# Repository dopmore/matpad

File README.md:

# matpad
a macropad for hackclub and CAD with EC11 rotary Encoder

Heres the final Version!

https://github.com/user-attachments/assets/6c2f23e0-6682-42b4-9371-2d59c67244ef

# BOM:

    - 16x Cherry MX Switches (+1 Just in Case?)
    - 15x DSA Keycaps
    - 16x Diodes (1N4148)
    - 4x M3x5x4 Heatset inserts (After I build the PCB i might remake the case to use screws)
    - 4x M3x16mm SHCS Bolts
    - 1x EC11 Rotary Encoder
    - 1x XIAO RP2040
    - 1x custom PCB

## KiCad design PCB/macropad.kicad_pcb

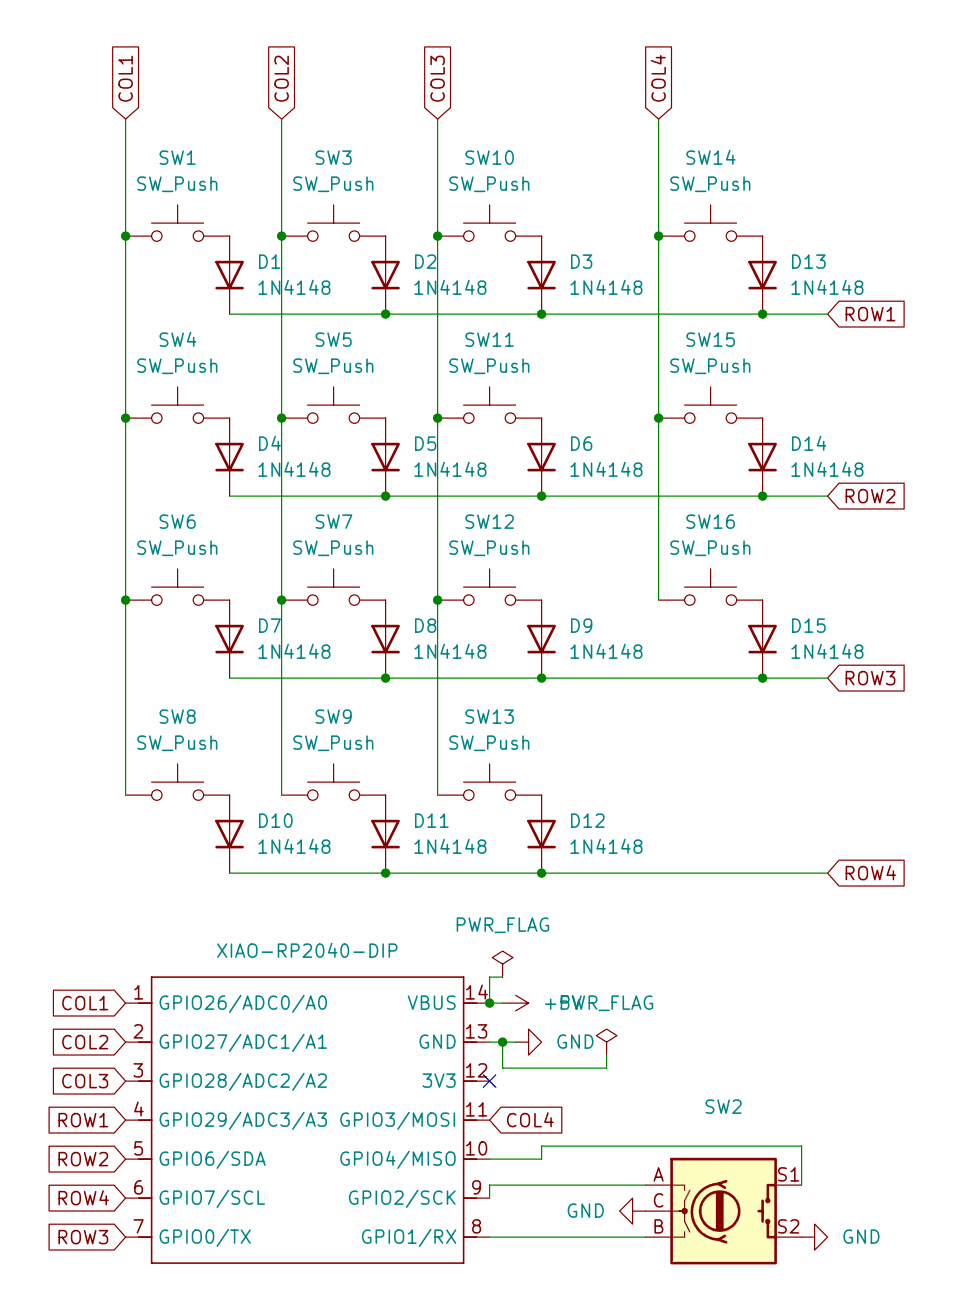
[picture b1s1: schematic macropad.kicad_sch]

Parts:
D1, D2, D3, D4, D5, D6, D7, D8, D9, D10, D11, D12, D13, D14, D15: 1N4148; D_DO-35_SOD27_P7.62mm_Horizontal
SW1, SW3, SW4, SW5, SW6, SW7, SW8, SW9, SW10, SW11, SW12, SW13, SW14, SW15, SW16: SW_Push; SW_Cherry_MX_1.00u_PCB
SW2: RotaryEncoder_Switch; RotaryEncoder_Alps_EC11E-Switch_Vertical_H20mm
U1: XIAO-RP2040-DIP

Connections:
+5V: U1.14 (VBUS)
COL1: SW1.1, SW4.1, SW6.1, SW8.1, U1.1 (GPIO26/ADC0/A0)
COL2: SW3.1, SW5.1, SW7.1, SW9.1, U1.2 (GPIO27/ADC1/A1)
COL3: SW10.1, SW11.1, SW12.1, SW13.1, U1.3 (GPIO28/ADC2/A2)
COL4: SW14.1, SW15.1, SW16.1, U1.11 (GPIO3/MOSI)
GND: SW2.C, SW2.S2, U1.13 (GND)
unnamed: D1.2 (A), SW1.2
unnamed: D2.2 (A), SW3.2
unnamed: D3.2 (A), SW10.2
unnamed: D4.2 (A), SW4.2
unnamed: D5.2 (A), SW5.2
unnamed: D6.2 (A), SW11.2
unnamed: D7.2 (A), SW6.2
unnamed: D8.2 (A), SW7.2
unnamed: D9.2 (A), SW12.2
unnamed: D10.2 (A), SW8.2
unnamed: D11.2 (A), SW9.2
unnamed: D12.2 (A), SW13.2
unnamed: D13.2 (A), SW14.2
unnamed: D14.2 (A), SW15.2
unnamed: D15.2 (A), SW16.2
unnamed: SW2.B, U1.8 (GPIO1/RX)
unnamed: SW2.A, U1.9 (GPIO2/SCK)
unnamed: SW2.S1, U1.10 (GPIO4/MISO)
ROW1: D1.1 (K), D2.1 (K), D3.1 (K), D13.1 (K), U1.4 (GPIO29/ADC3/A3)
ROW2: D4.1 (K), D5.1 (K), D6.1 (K), D14.1 (K), U1.5 (GPIO6/SDA)
ROW3: D7.1 (K), D8.1 (K), D9.1 (K), D15.1 (K), U1.7 (GPIO0/TX)
ROW4: D10.1 (K), D11.1 (K), D12.1 (K), U1.6 (GPIO7/SCL)

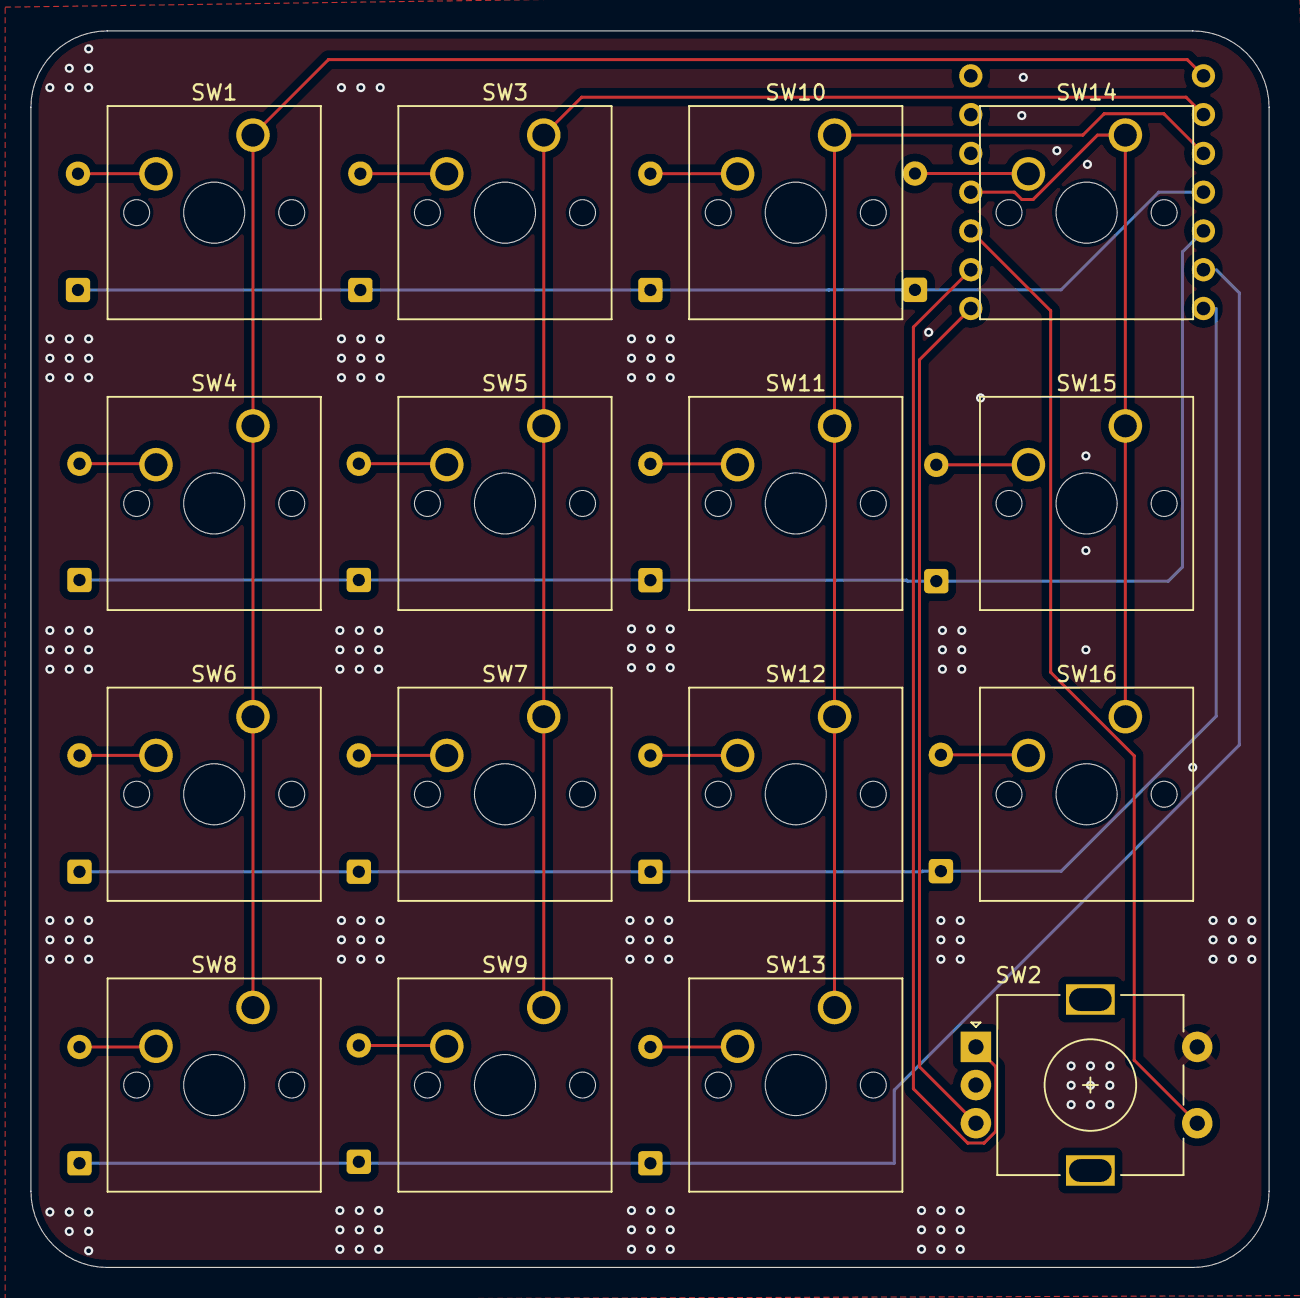
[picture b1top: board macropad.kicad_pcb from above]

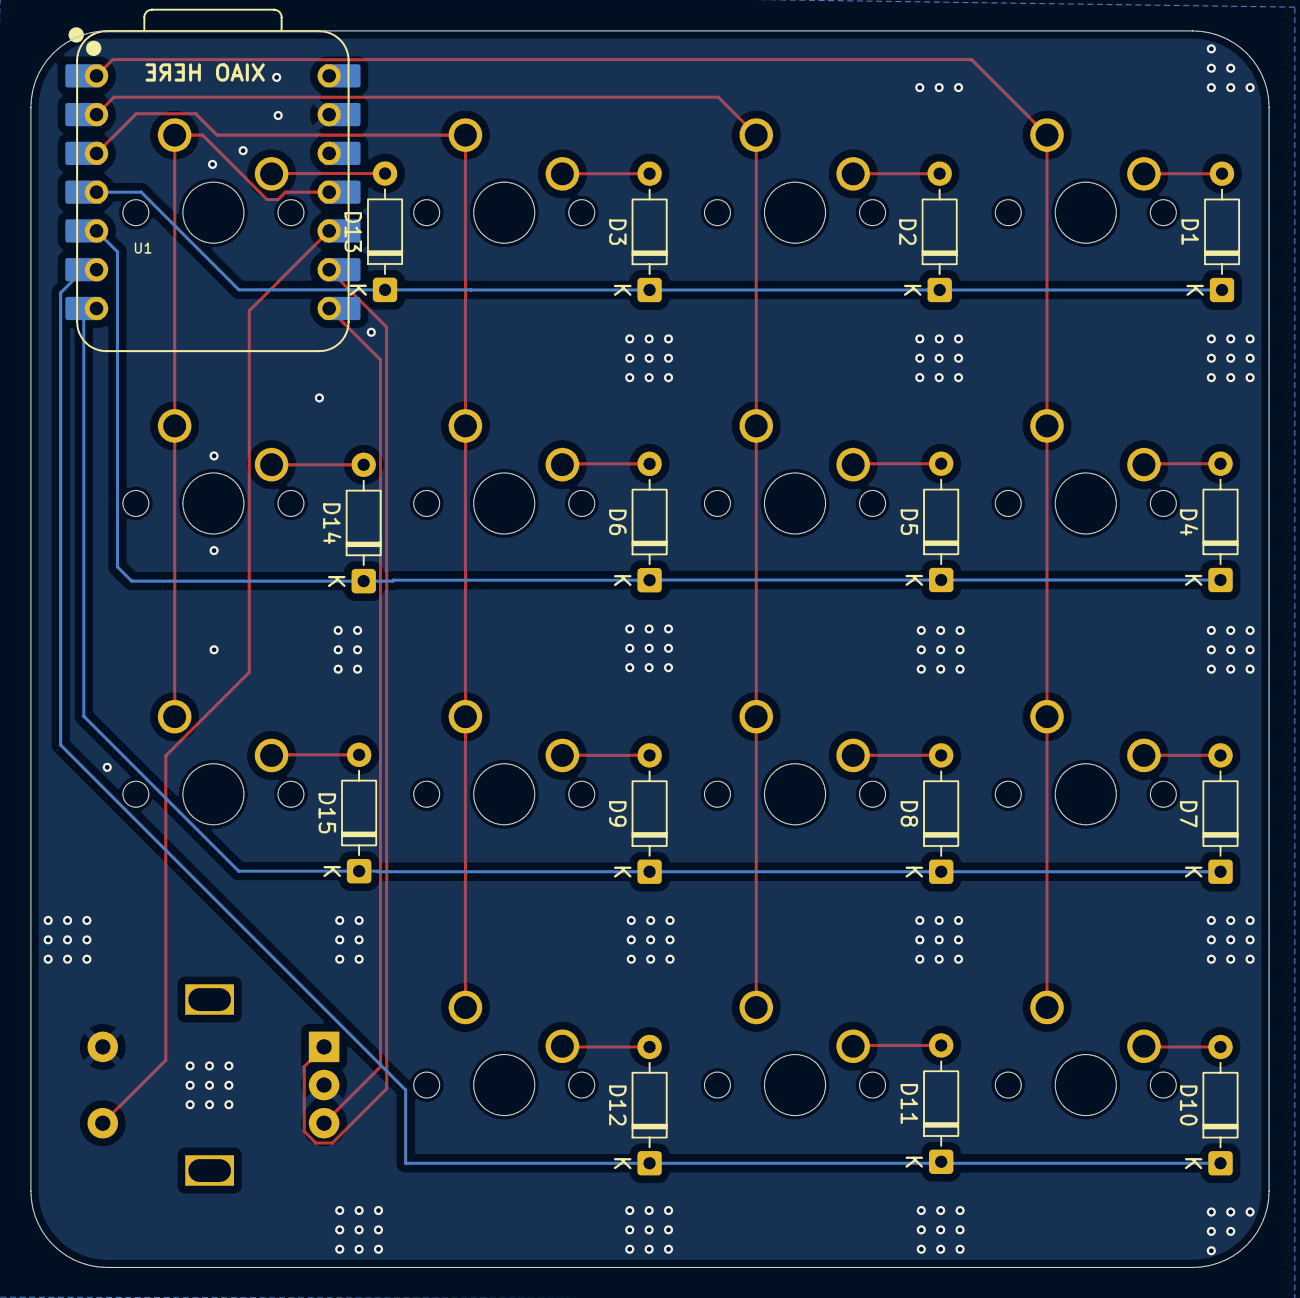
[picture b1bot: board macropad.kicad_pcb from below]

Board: 2 copper layers, 81.1 x 81.0 mm, 32 parts (16 on the bottom side), 27 nets.

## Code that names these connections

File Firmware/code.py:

import board
from kmk.kmk_keyboard import KMKKeyboard
from kmk.keys import KC
from kmk.scanners import DiodeOrientation
from kmk.extensions.RGB import RGB, AnimationModes
from kmk.extensions.media_keys import MediaKeys
from kmk.modules.encoder import EncoderHandler

# Pinout
COL1 = board.D0
COL2 = board.D1
COL3 = board.D2
COL4 = board.D10
ROW1 = board.D3
ROW2 = board.D4
ROW3 = board.D5
ROW4 = board.D6
PUSHBUTTON = board.D9
ROTA = board.D8
ROTB = board.D7


keyboard = KMKKeyboard()

# Basic matrix settings
keyboard.col_pins = (COL1, COL2, COL3, COL4)
keyboard.row_pins = (ROW1, ROW2, ROW3, ROW4)
keyboard.diode_orientation = DiodeOrientation.COL2ROW

keyboard.extensions.append(MediaKeys())

# Encoder settings
encoder_handler = EncoderHandler()
keyboard.modules.append(encoder_handler)
encoder_handler.pins = ((ROTA, ROTB, PUSHBUTTON, False),)
encoder_handler.map = (((KC.VOLD, KC.VOLU, KC.KP_ENTER),),)

# Keymap
keyboard.keymap = [[
        # 16 matrix keys (row-major order)
        KC.KP_1, KC.KP_2, KC.KP_3, KC.NUMLOCK,
        KC.KP_4, KC.KP_5, KC.KP_6, KC.KP_ASTERISK,
        KC.DOT,  KC.KP_0, KC.KP_PLUS, KC.KP_ENTER,
        KC.KP_7, KC.KP_8, KC.KP_9, KC.KP_MINUS,
        
        

        # Encoder virtual keys (MUST exist even if mapped elsewhere)
        KC.VOLD,   # encoder CCW
        KC.VOLU,   # encoder CW
        KC.MUTE,   # encoder button
        ]
]


if __name__ == '__main__':
    keyboard.go()

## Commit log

2025-12-20 done
2025-12-20 Enhance README with images and BOM information
    Added images and BOM details to the README.
2025-12-20 Update README to include CAD in description
2025-12-20 Redesign
2025-12-20 Enhance README with images and updated BOM
    Updated the README to include additional images and BOM details.
2025-12-20 Fix row pin reference in main.py
2025-12-21 Aktualisieren von README.md
2025-12-21 Revise BOM and add additional images to README
    Updated the bill of materials and added new images.
2025-12-21 minimalist case
2025-12-21 Enhance README with images and BOM updates
    Updated README with additional images and BOM details.
2025-12-21 Remove duplicate image entry
    Removed duplicate image from README.
2025-12-23 Added vias for ground plane
2025-12-23 Replace an image in README with a new one
2026-02-14 Firmaware to put on XIAO
